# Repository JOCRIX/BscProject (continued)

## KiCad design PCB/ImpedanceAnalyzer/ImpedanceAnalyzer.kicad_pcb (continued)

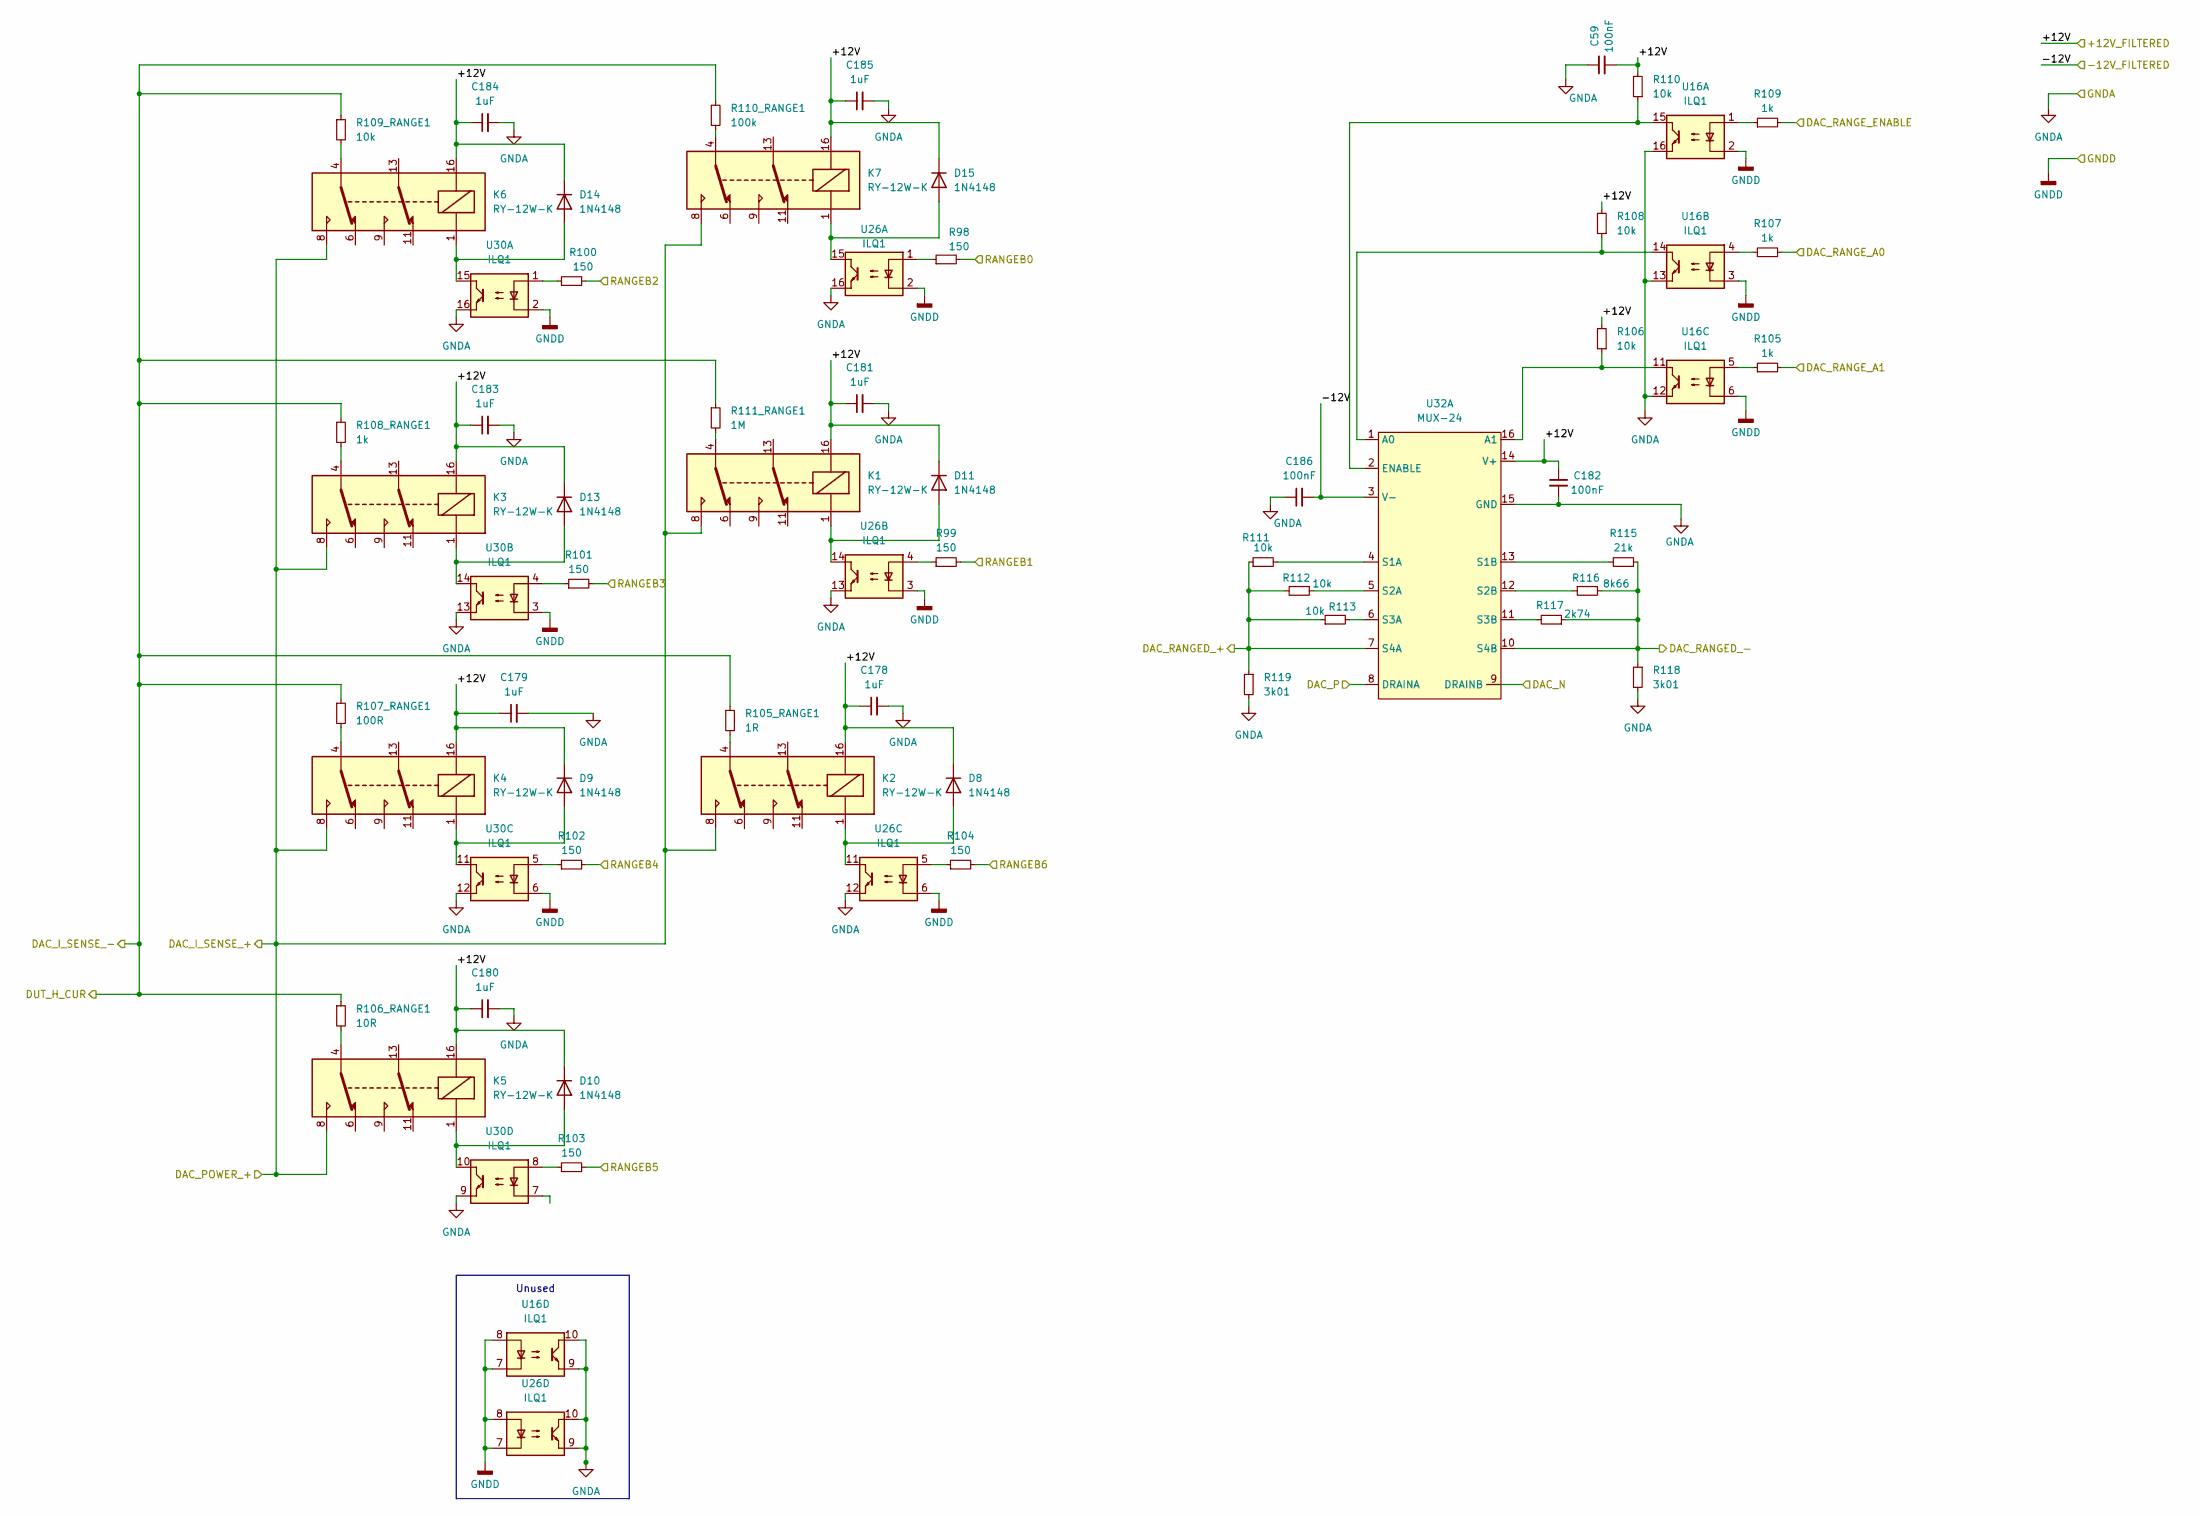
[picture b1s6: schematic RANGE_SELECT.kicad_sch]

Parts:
C59, C182, C186: 100nF; C_0805_2012Metric_Pad1.18x1.45mm_HandSolder
C178, C179, C180, C181, C183, C184, C185: 1uF; C_0805_2012Metric_Pad1.18x1.45mm_HandSolder
D8, D9, D10, D11, D13, D14, D15: 1N4148; D_DO-35_SOD27_P7.62mm_Horizontal
K1, K2, K3, K4, K5, K6, K7: RY-12W-K; RELAY_RY-12W-K
R98, R99, R100, R101, R102, R103, R104: 150; R_0805_2012Metric_Pad1.20x1.40mm_HandSolder
R105, R107, R109: 1k; R_0805_2012Metric_Pad1.20x1.40mm_HandSolder
R105_RANGE1: 1R; R_Axial_DIN0516_L15.5mm_D5.0mm_P20.32mm_Horizontal
R106, R108, R110: 10k; R_0805_2012Metric_Pad1.20x1.40mm_HandSolder
R106_RANGE1: 10R; R_Axial_DIN0207_L6.3mm_D2.5mm_P10.16mm_Horizontal
R107_RANGE1: 100R; R_Axial_DIN0207_L6.3mm_D2.5mm_P10.16mm_Horizontal
R108_RANGE1: 1k; R_Axial_DIN0207_L6.3mm_D2.5mm_P10.16mm_Horizontal
R109_RANGE1, R111, R112, R113: 10k; R_Axial_DIN0207_L6.3mm_D2.5mm_P10.16mm_Horizontal
R110_RANGE1: 100k; R_Axial_DIN0207_L6.3mm_D2.5mm_P10.16mm_Horizontal
R111_RANGE1: 1M; R_Axial_DIN0207_L6.3mm_D2.5mm_P10.16mm_Horizontal
R115: 21k; R_Axial_DIN0207_L6.3mm_D2.5mm_P10.16mm_Horizontal
R116: 8k66; R_Axial_DIN0207_L6.3mm_D2.5mm_P10.16mm_Horizontal
R117: 2k74; R_Axial_DIN0207_L6.3mm_D2.5mm_P10.16mm_Horizontal
R118, R119: 3k01; R_Axial_DIN0207_L6.3mm_D2.5mm_P10.16mm_Horizontal
U16, U26, U30: ILQ1; DIP-16_W7.62mm
U32: MUX-24; DIP-16_W7.62mm

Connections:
/ADC Range/+12V: C59.2, C178.1, C179.1, C180.1, C181.1, C182.1, C183.1, C184.1, C185.1, D8.1 (K), D9.1 (K), D10.1 (K), D11.1 (K), D13.1 (K), D14.1 (K), D15.1 (K), K1.16, K2.16, K3.16, K4.16, K5.16, K6.16, K7.16, R106.2, R108.2, R110.2, U32.14 (V+); also elsewhere on the board
/ADC Range/-12V: C186.2, U32.3 (V-); also elsewhere on the board
/ADC Range/DUT_I_SENSE_+: K1.8, K2.8, K3.8, K4.8, K5.8, K6.8, K7.8; also elsewhere on the board
/ADC Range/DUT_I_SENSE_-: R105_RANGE1.1, R106_RANGE1.1, R107_RANGE1.1, R108_RANGE1.1, R109_RANGE1.1, R110_RANGE1.1, R111_RANGE1.1; also elsewhere on the board
/DAC Power Amp/DAC_RANGED_+: R111.1, R112.2, R113.1, R119.1, U32.7 (S4A); also elsewhere on the board
/DAC Power Amp/DAC_RANGED_-: R115.1, R116.2, R117.1, R118.1, U32.10 (S4B); also elsewhere on the board
/DAC/DAC_N: U32.9 (DRAINB); also elsewhere on the board
/DAC/DAC_P: U32.8 (DRAINA); also elsewhere on the board
/DRA0: R107.2; also elsewhere on the board
/DRA1: R105.2; also elsewhere on the board
/DRE: R109.2; also elsewhere on the board
/RB0: R98.2; also elsewhere on the board
/RB1: R99.2; also elsewhere on the board
/RB2: R100.2; also elsewhere on the board
/RB3: R101.2; also elsewhere on the board
/RB4: R102.2; also elsewhere on the board
/RB5: R103.2; also elsewhere on the board
/RB6: R104.2; also elsewhere on the board
unnamed: D8.2 (A), K2.1, U26.11
unnamed: D9.2 (A), K4.1, U30.11
unnamed: D10.2 (A), K5.1, U30.10
unnamed: D11.2 (A), K1.1, U26.14
unnamed: D13.2 (A), K3.1, U30.14
unnamed: D14.2 (A), K6.1, U30.15
unnamed: D15.2 (A), K7.1, U26.15
unnamed: K1.4, R111_RANGE1.2
unnamed: K2.4, R105_RANGE1.2
unnamed: K3.4, R108_RANGE1.2
unnamed: K4.4, R107_RANGE1.2
unnamed: K5.4, R106_RANGE1.2
unnamed: K6.4, R109_RANGE1.2
unnamed: K7.4, R110_RANGE1.2
unnamed: R98.1, U26.1
unnamed: R99.1, U26.4
unnamed: R100.1, U30.1
unnamed: R101.1, U30.4
unnamed: R102.1, U30.5
unnamed: R103.1, U30.8
unnamed: R104.1, U26.5
unnamed: R105.1, U16.5
unnamed: R107.1, U16.4
unnamed: R109.1, U16.1
unnamed: R108.1, U16.14, U32.1 (A0)
unnamed: R106.1, U16.11, U32.16 (A1)
unnamed: R110.1, U16.15, U32.2 (ENABLE)
unnamed: R111.2, U32.4 (S1A)
unnamed: R115.2, U32.13 (S1B)
unnamed: R112.1, U32.5 (S2A)
unnamed: R116.1, U32.12 (S2B)
unnamed: R113.2, U32.6 (S3A)
unnamed: R117.2, U32.11 (S3B)

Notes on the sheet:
Unused

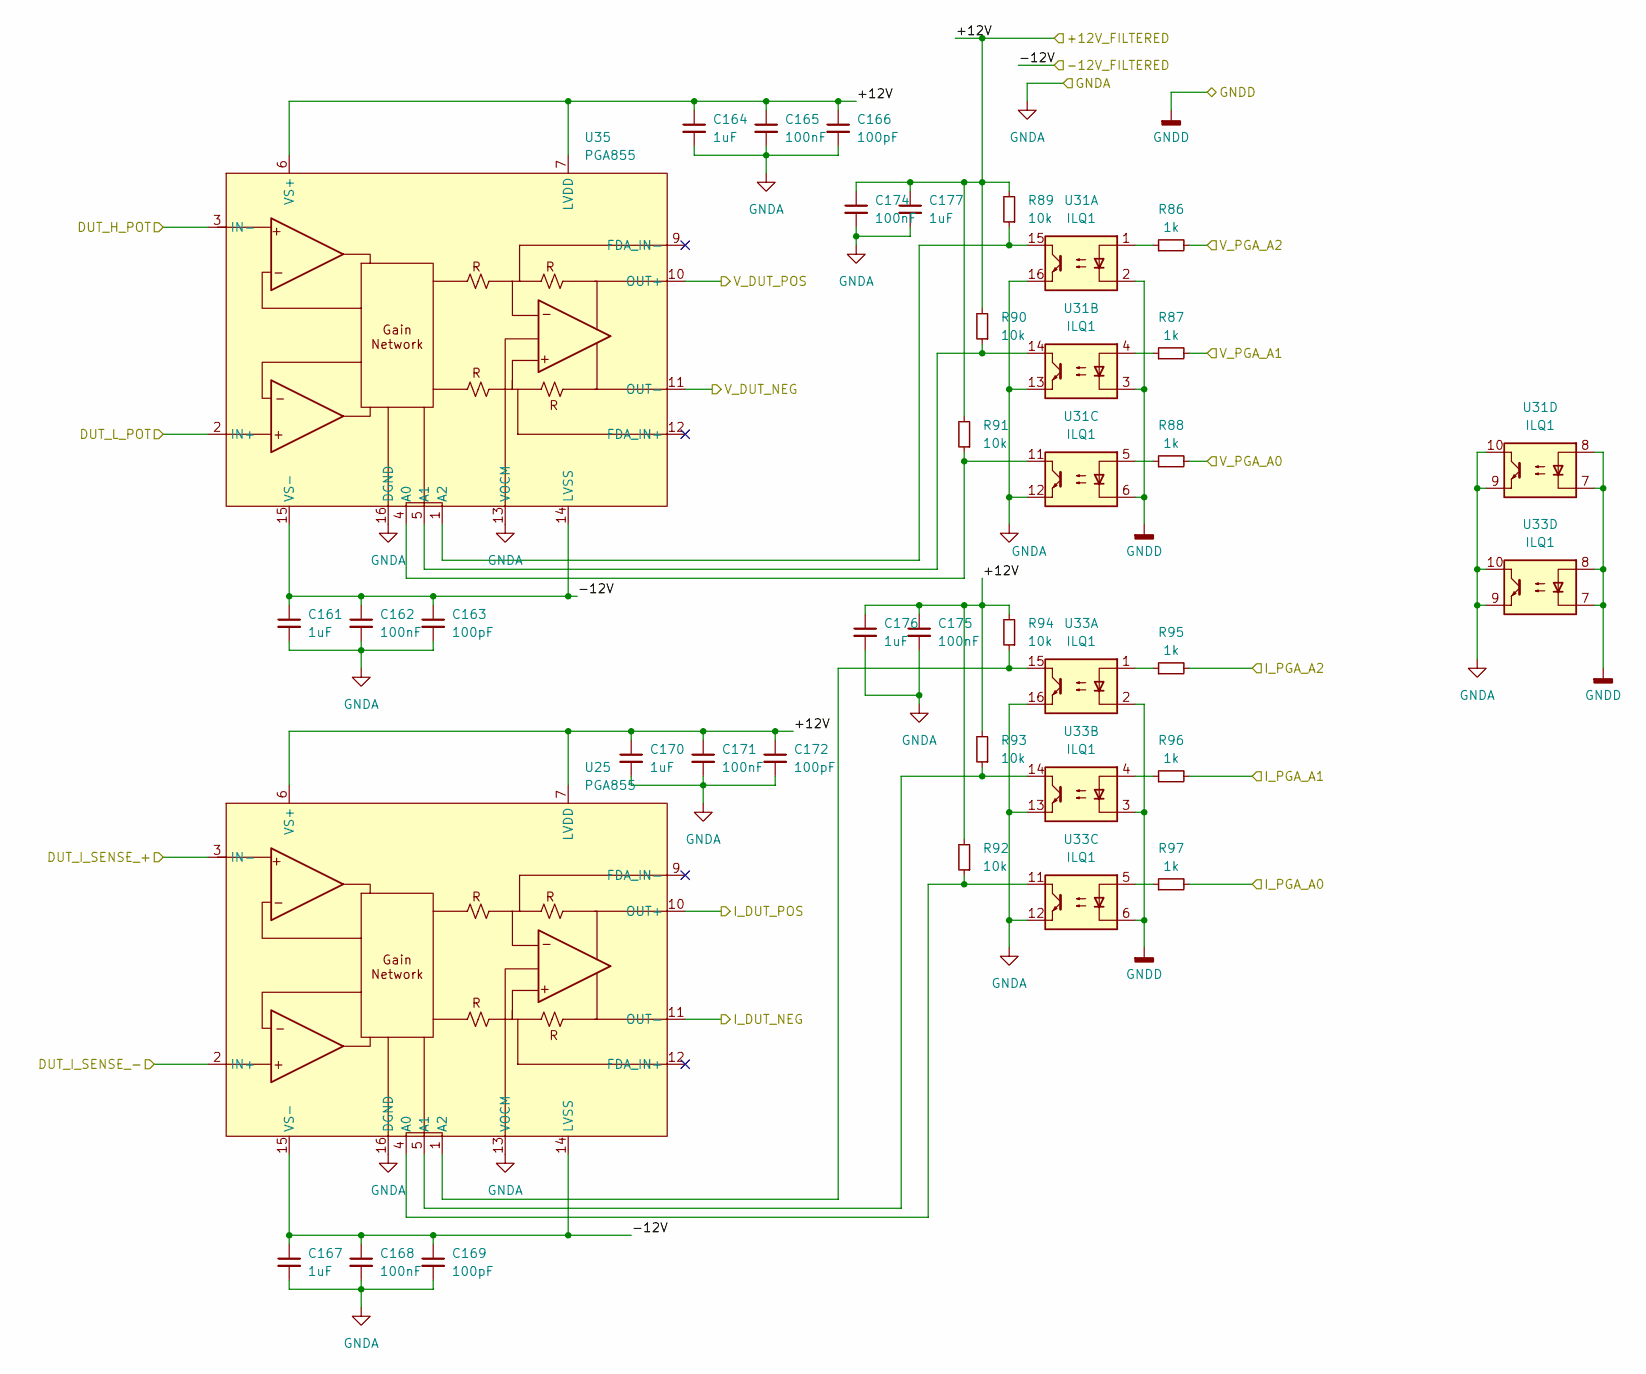
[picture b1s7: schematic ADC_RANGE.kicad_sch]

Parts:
C161, C164, C167, C170, C176, C177: 1uF; C_0805_2012Metric_Pad1.18x1.45mm_HandSolder
C162, C165, C168, C171, C174, C175: 100nF; C_0805_2012Metric_Pad1.18x1.45mm_HandSolder
C163, C166, C169, C172: 100pF; C_Disc_D3.4mm_W2.1mm_P2.50mm
R86, R87, R88, R95, R96, R97: 1k; R_0805_2012Metric_Pad1.20x1.40mm_HandSolder
R89, R90, R91, R92, R93, R94: 10k; R_0805_2012Metric_Pad1.20x1.40mm_HandSolder
U25, U35: PGA855; VQFN-16-1EP_3x3mm_P0.5mm_EP1.45x1.45mm
U31, U33: ILQ1; DIP-16_W7.62mm

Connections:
/ADC Range/+12V: C164.1, C165.1, C166.1, C170.1, C171.1, C172.1, C174.1, C175.1, C176.1, C177.1, R89.2, R90.2, R91.2, R92.2, R93.2, R94.2, U25.6 (VS+), U25.7 (LVDD), U35.6 (VS+), U35.7 (LVDD); also elsewhere on the board
/ADC Range/-12V: C161.1, C162.1, C163.1, C167.1, C168.1, C169.1, U25.14 (LVSS), U25.15 (VS-), U35.14 (LVSS), U35.15 (VS-); also elsewhere on the board
/ADC Range/DUT_H_POT: U35.3 (IN-); also elsewhere on the board
/ADC Range/DUT_I_SENSE_+: U25.3 (IN-); also elsewhere on the board
/ADC Range/DUT_I_SENSE_-: U25.2 (IN+); also elsewhere on the board
/ADC Range/DUT_L_POT: U35.2 (IN+); also elsewhere on the board
/ADC Range/I_DUT_NEG: U25.11 (OUT-); also elsewhere on the board
/ADC Range/I_DUT_POS: U25.10 (OUT+); also elsewhere on the board
/ADC Range/I_PGA_A0: R97.2; also elsewhere on the board
/ADC Range/I_PGA_A1: R96.2; also elsewhere on the board
/ADC Range/I_PGA_A2: R95.2; also elsewhere on the board
/ADC Range/V_DUT_NEG: U35.11 (OUT-); also elsewhere on the board
/ADC Range/V_DUT_POS: U35.10 (OUT+); also elsewhere on the board
/ADC Range/V_PGA_A0: R88.2; also elsewhere on the board
/ADC Range/V_PGA_A1: R87.2; also elsewhere on the board
/ADC Range/V_PGA_A2: R86.2; also elsewhere on the board
unnamed: R86.1, U31.1
unnamed: R87.1, U31.4
unnamed: R88.1, U31.5
unnamed: R95.1, U33.1
unnamed: R96.1, U33.4
unnamed: R97.1, U33.5
unnamed: R92.1, U25.4 (A0), U33.11
unnamed: R93.1, U25.5 (A1), U33.14
unnamed: R94.1, U25.1 (A2), U33.15
unnamed: R91.1, U31.11, U35.4 (A0)
unnamed: R90.1, U31.14, U35.5 (A1)
unnamed: R89.1, U31.15, U35.1 (A2)

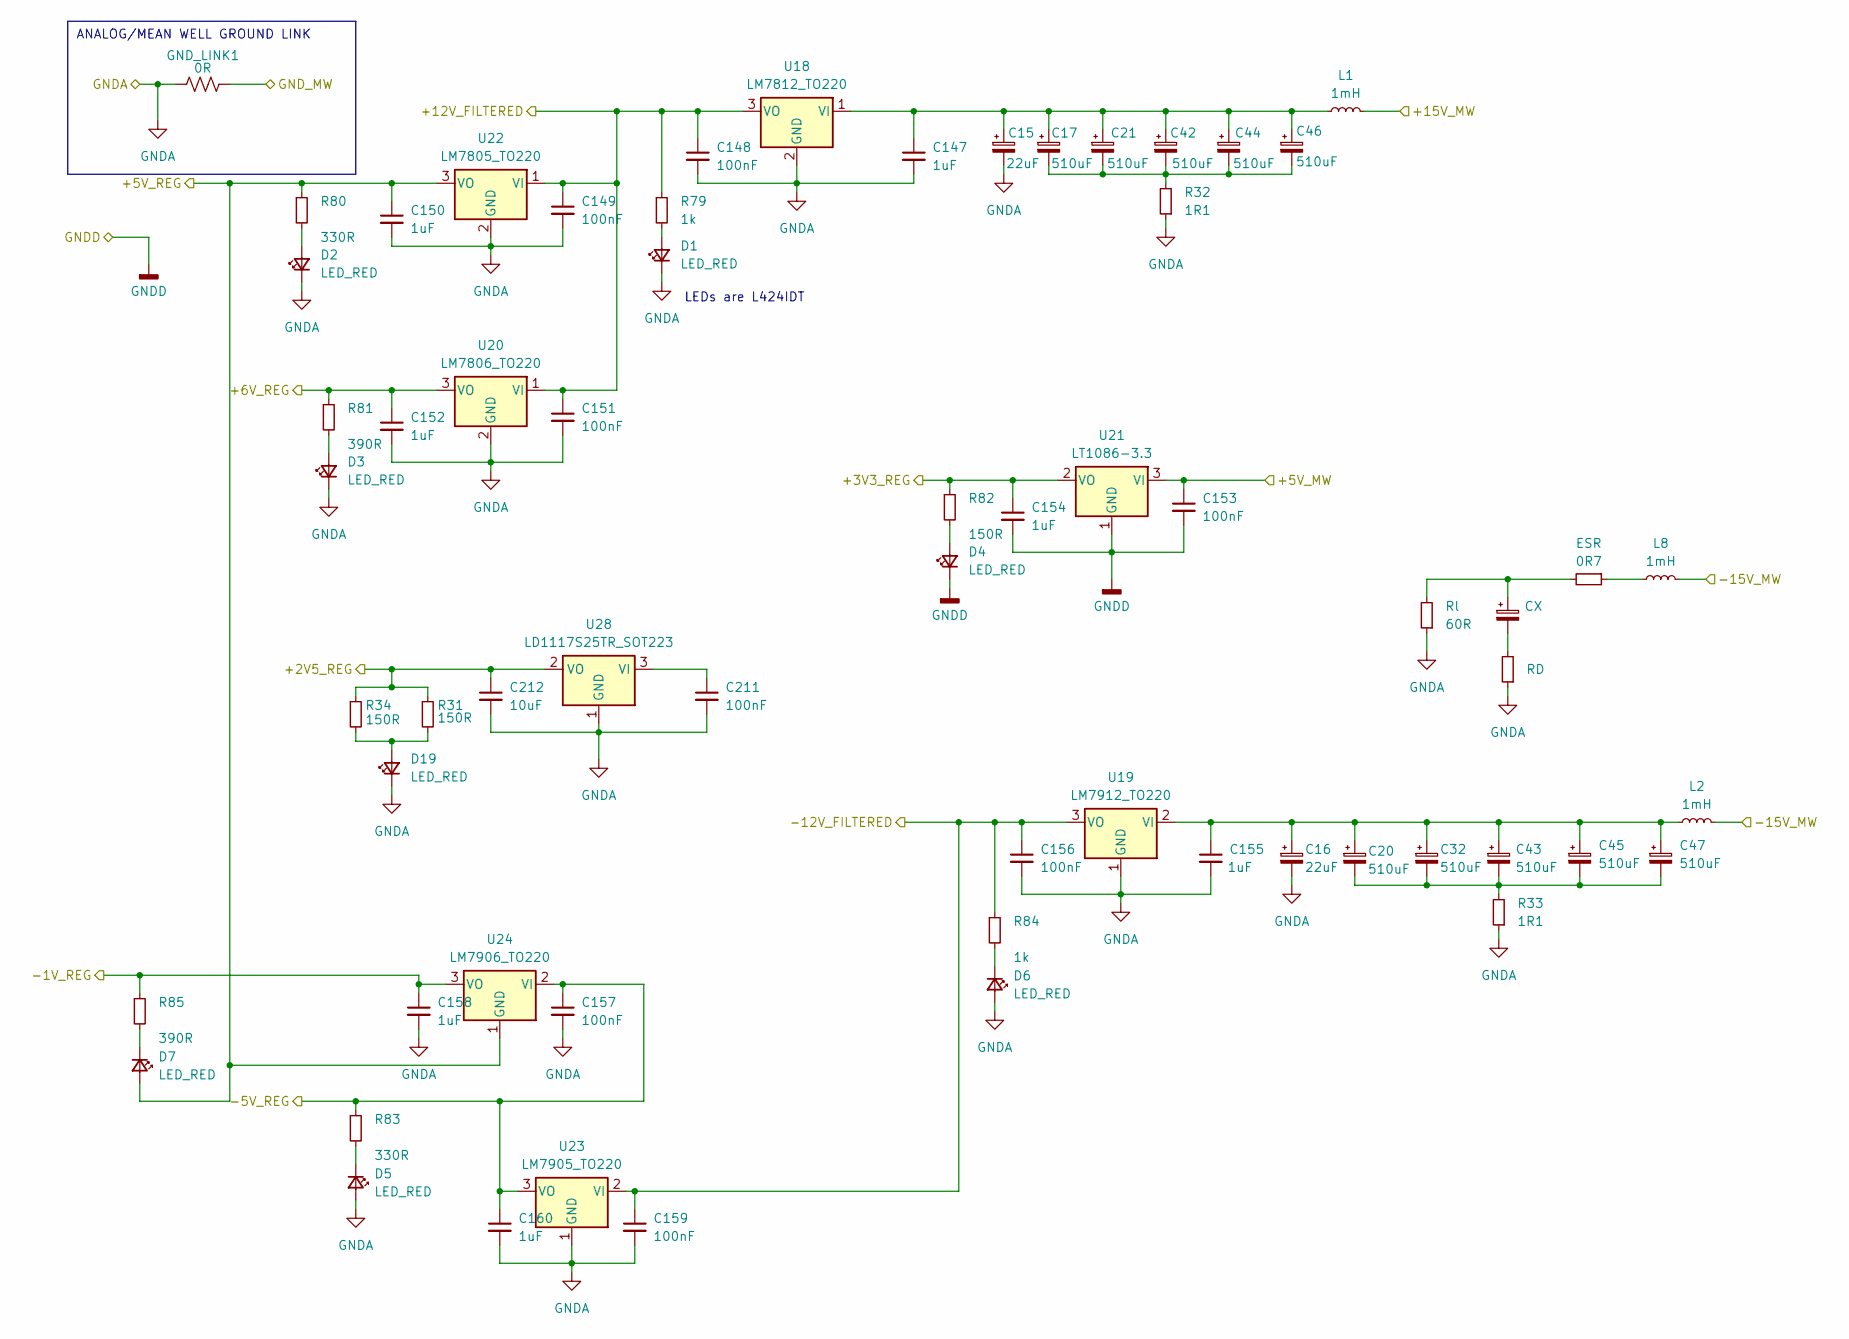
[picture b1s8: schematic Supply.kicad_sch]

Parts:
C15, C16: 22uF; CP_Radial_D6.3mm_P2.50mm
C17, C20, C21, C32, C42, C43, C44, C45, C46, C47: 510uF; CP_Radial_D10.0mm_P5.00mm
C147, C150, C152, C154, C155, C158, C160: 1uF; C_0805_2012Metric_Pad1.18x1.45mm_HandSolder
C148, C149, C151, C153, C156, C157, C159, C211: 100nF; C_0805_2012Metric_Pad1.18x1.45mm_HandSolder
C212: 10uF; C_1210_3225Metric
CX: CX; CP_Radial_D10.0mm_P5.00mm
D1, D2, D3, D4, D5, D6, D7, D19: LED_RED; LED_D2.0mm_W4.0mm_H2.8mm_FlatTop
ESR: 0R7; R_Axial_DIN0207_L6.3mm_D2.5mm_P10.16mm_Horizontal
GND_LINK1: 0R; Resistor SMD - 2818
L1, L2, L8: 1mH; INDRD1000W100D1800H2550 - AIUR-15-102K
R31, R34, R82: 150R; R_Axial_DIN0207_L6.3mm_D2.5mm_P10.16mm_Horizontal
R32, R33: 1R1; R_Axial_DIN0207_L6.3mm_D2.5mm_P10.16mm_Horizontal
R35: RD; R_Axial_DIN0207_L6.3mm_D2.5mm_P10.16mm_Horizontal
R79, R84: 1k; R_Axial_DIN0207_L6.3mm_D2.5mm_P10.16mm_Horizontal
R80, R83: 330R; R_Axial_DIN0207_L6.3mm_D2.5mm_P10.16mm_Horizontal
R81, R85: 390R; R_Axial_DIN0207_L6.3mm_D2.5mm_P10.16mm_Horizontal
Rl: 60R; R_Axial_DIN0207_L6.3mm_D2.5mm_P10.16mm_Horizontal
U18: LM7812_TO220; TO-220-3_Vertical
U19: LM7912_TO220; TO-220-3_Vertical
U20: LM7806_TO220; TO-220-3_Vertical
U21: LT1086-3.3; TO-220-3_Vertical
U22: LM7805_TO220; TO-220-3_Vertical
U23: LM7905_TO220; TO-220-3_Vertical
U24: LM7906_TO220; TO-220-3_Vertical
U28: LD1117S25TR_SOT223; SOT-223-3_TabPin2

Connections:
/+5V_MW: C153.1, U21.3 (VI); also elsewhere on the board
/+15V_MW: L1.2; also elsewhere on the board
/-15V_MW: L2.2, L8.2; also elsewhere on the board
/ADC Range/+12V: C148.1, C149.1, C151.1, R79.1, U18.3 (VO), U20.1 (VI), U22.1 (VI); also elsewhere on the board
/ADC Range/-12V: C156.1, C159.1, R84.1, U19.3 (VO), U23.2 (VI); also elsewhere on the board
/ADC/+2V5: C212.1, R31.1, R34.1, U28.2 (VO); also elsewhere on the board
/ADC/+6V: C152.1, R81.1, U20.3 (VO); also elsewhere on the board
/ADC/-1V: C158.1, R85.1, U24.3 (VO); also elsewhere on the board
/Digital/+3V3: C154.1, R82.1, U21.2 (VO); also elsewhere on the board
/GND_MW: GND_LINK1.2; also elsewhere on the board
unnamed: C17.2, C21.2, C42.2, C44.2, C46.2, R32.2
unnamed: CX.1, ESR.2, Rl.2
unnamed: CX.2, R35.2
unnamed: D1.2 (A), R79.2
unnamed: D2.2 (A), R80.2
unnamed: D3.2 (A), R81.2
unnamed: D4.2 (A), R82.2
unnamed: D5.1 (K), R83.2
unnamed: D6.1 (K), R84.2
unnamed: D7.1 (K), R85.2
unnamed: D19.2 (A), R31.2, R34.2
unnamed: ESR.1, L8.1
unnamed: C15.1, C17.1, C21.1, C42.1, C44.1, C46.1, C147.1, L1.1, U18.1 (VI)

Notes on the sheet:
LEDs are L424IDT
ANALOG/MEAN WELL GROUND LINK

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
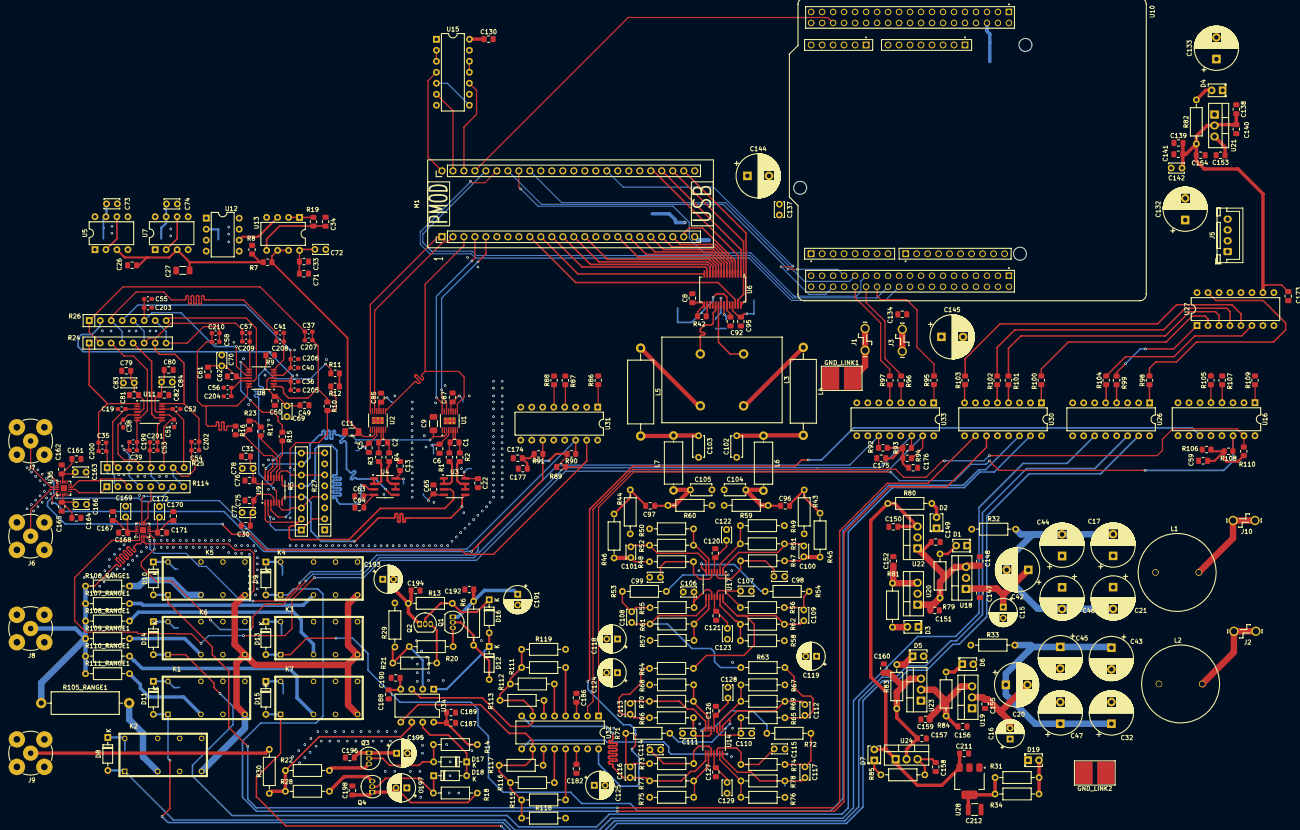
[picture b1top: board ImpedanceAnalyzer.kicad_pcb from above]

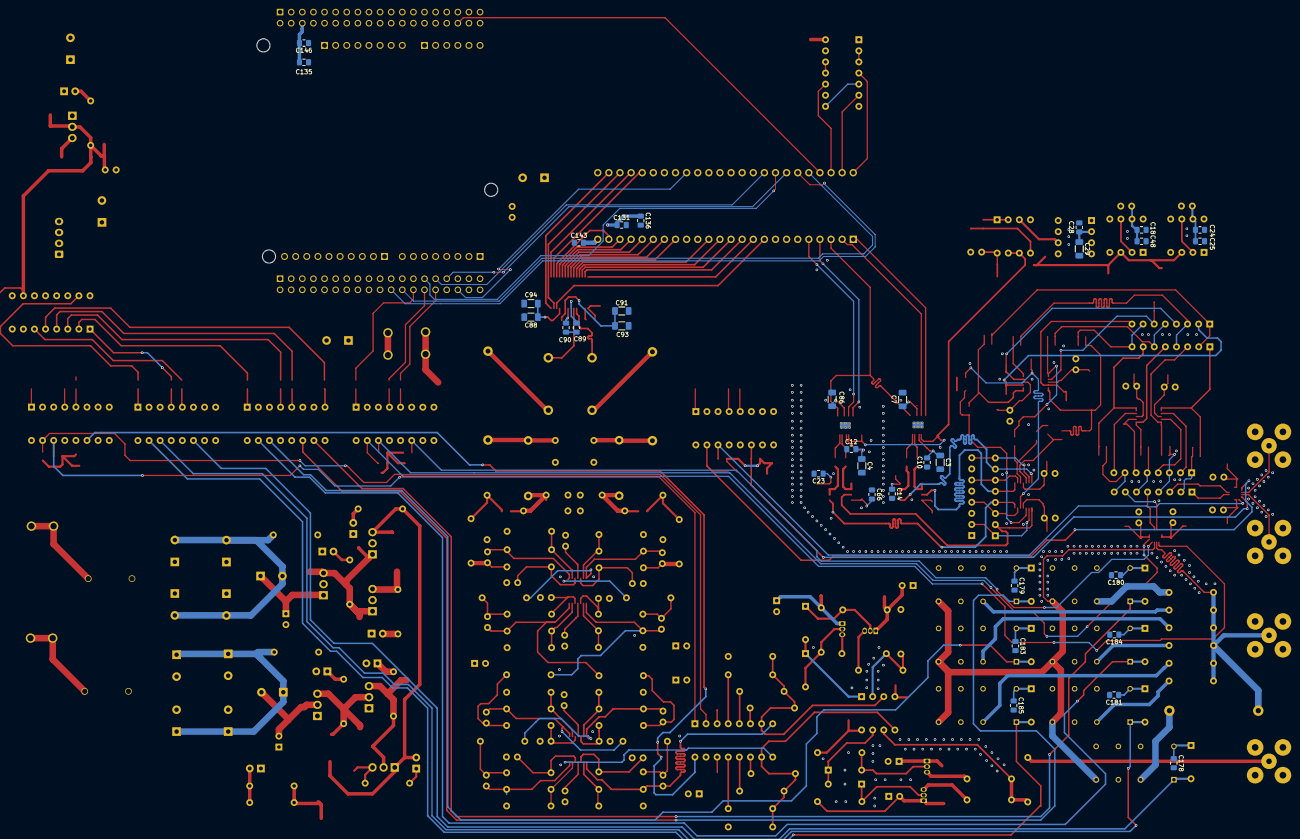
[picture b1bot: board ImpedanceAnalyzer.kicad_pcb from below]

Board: 4 copper layers, 411 parts (33 on the bottom side), 258 nets.

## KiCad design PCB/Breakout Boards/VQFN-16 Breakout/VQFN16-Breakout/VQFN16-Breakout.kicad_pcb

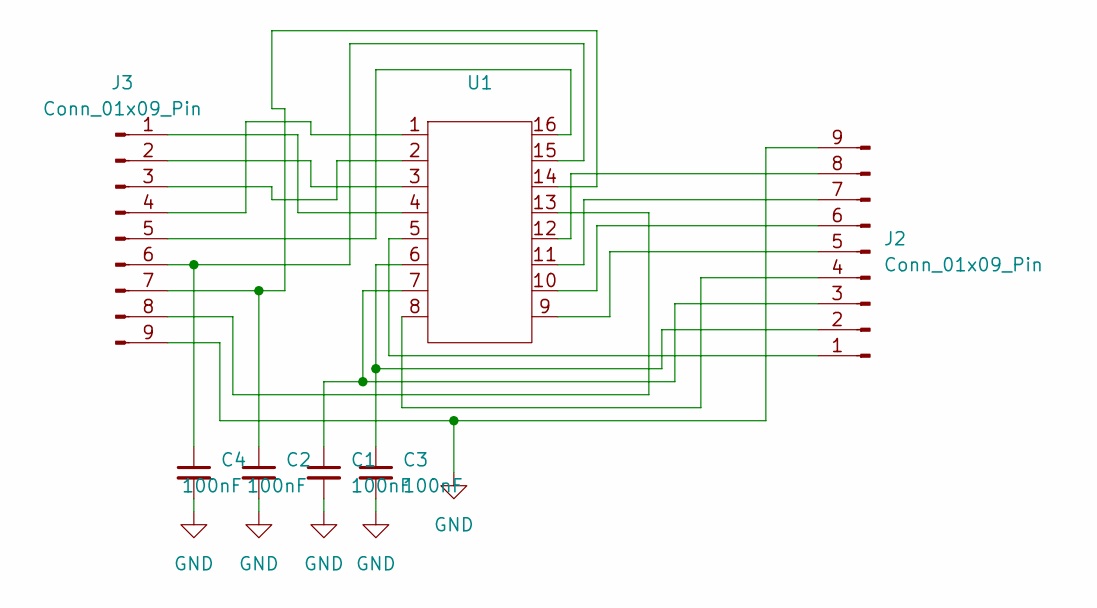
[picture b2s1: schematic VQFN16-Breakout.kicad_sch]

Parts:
C1, C2, C3, C4: 100nF; C_0805_2012Metric
J2, J3: Conn_01x09_Pin; PinHeader_1x09_P2.54mm_Vertical
U1: VQFN-16-1EP_3x3mm_P0.5mm_EP1.45x1.45mm

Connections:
GND: C1.2, C2.2, C3.2, C4.2, J2.9, J3.9
unnamed: J2.1, U1.5
unnamed: C3.1, J2.2, U1.6
unnamed: C1.1, J2.3, U1.7
unnamed: J2.4, U1.8
unnamed: J2.5, U1.9
unnamed: J2.6, U1.10
unnamed: J2.7, U1.11
unnamed: J2.8, U1.12
unnamed: J3.1, U1.4
unnamed: J3.2, U1.3
unnamed: J3.3, U1.2
unnamed: J3.4, U1.1
unnamed: J3.5, U1.16
unnamed: C4.1, J3.6, U1.15
unnamed: C2.1, J3.7, U1.14
unnamed: J3.8, U1.13

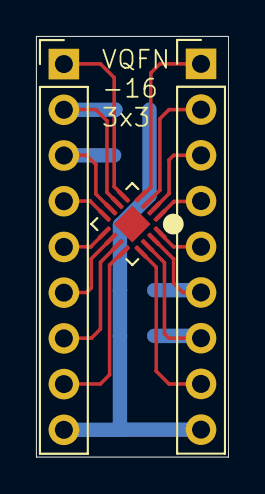
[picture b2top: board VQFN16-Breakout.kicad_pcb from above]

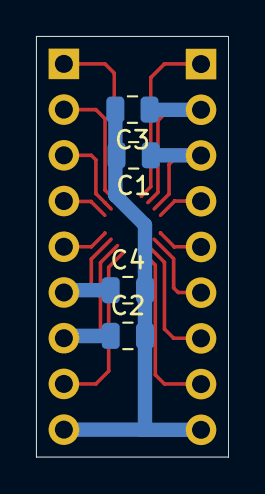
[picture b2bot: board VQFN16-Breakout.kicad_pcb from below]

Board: 2 copper layers, 10.7 x 23.4 mm, 7 parts (4 on the bottom side), 17 nets.

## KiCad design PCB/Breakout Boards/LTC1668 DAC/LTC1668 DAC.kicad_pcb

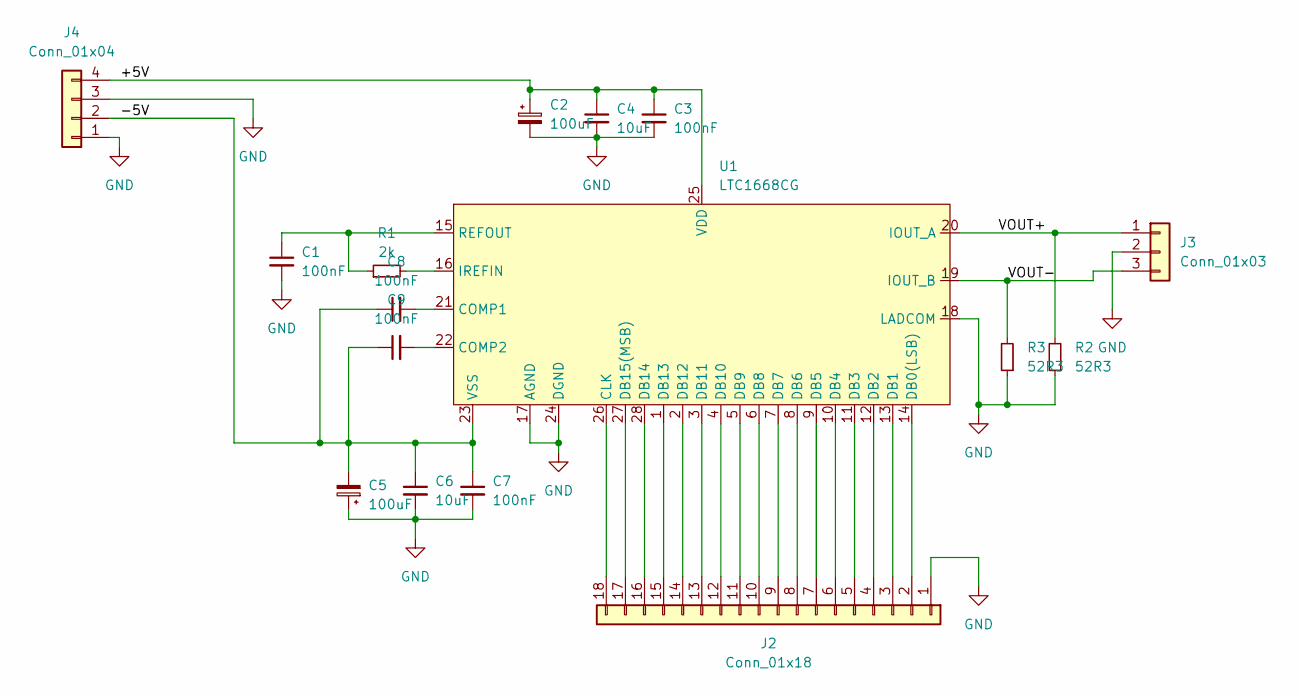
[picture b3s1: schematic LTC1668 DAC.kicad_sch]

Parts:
C1, C3, C7, C8, C9: 100nF; C_0805_2012Metric_Pad1.18x1.45mm_HandSolder
C2, C5: 100uF; CP_Radial_D6.3mm_P2.50mm
C4, C6: 10uF; C_1206_3216Metric_Pad1.33x1.80mm_HandSolder
J2: Conn_01x18; PinHeader_1x18_P2.54mm_Vertical
J3: Conn_01x03; PinHeader_1x03_P2.54mm_Vertical
J4: Conn_01x04; PinHeader_1x04_P2.54mm_Vertical
R1: 2k; R_0805_2012Metric_Pad1.20x1.40mm_HandSolder
R2, R3: 52R3; R_0805_2012Metric_Pad1.20x1.40mm_HandSolder
U1: LTC1668CG; SSOP-28_5.3x10.2mm_P0.65mm

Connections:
/+5V: C2.1, C3.1, C4.1, J4.4, U1.25 (VDD)
/-5V: C5.2, C6.1, C7.1, C8.1, C9.1, J4.2, U1.23 (VSS)
/VOUT+: J3.1, R2.2, U1.20 (IOUT_A)
/VOUT-: J3.3, R3.2, U1.19 (IOUT_B)
GND: C1.2, C2.2, C3.2, C4.2, C5.1, C6.2, C7.2, J2.1, J3.2, J4.1, J4.3, R2.1, R3.1, U1.17 (AGND), U1.18 (LADCOM), U1.24 (DGND)
unnamed: J2.2, U1.14 (DB0(LSB))
unnamed: J2.3, U1.13 (DB1)
unnamed: J2.4, U1.12 (DB2)
unnamed: J2.5, U1.11 (DB3)
unnamed: J2.6, U1.10 (DB4)
unnamed: J2.7, U1.9 (DB5)
unnamed: J2.8, U1.8 (DB6)
unnamed: J2.9, U1.7 (DB7)
unnamed: J2.10, U1.6 (DB8)
unnamed: J2.11, U1.5 (DB9)
unnamed: J2.12, U1.4 (DB10)
unnamed: J2.13, U1.3 (DB11)
unnamed: J2.14, U1.2 (DB12)
unnamed: J2.15, U1.1 (DB13)
unnamed: J2.16, U1.28 (DB14)
unnamed: J2.17, U1.27 (DB15(MSB))
unnamed: J2.18, U1.26 (CLK)
unnamed: C8.2, U1.21 (COMP1)
unnamed: C9.2, U1.22 (COMP2)
unnamed: R1.2, U1.16 (IREFIN)
unnamed: C1.1, R1.1, U1.15 (REFOUT)

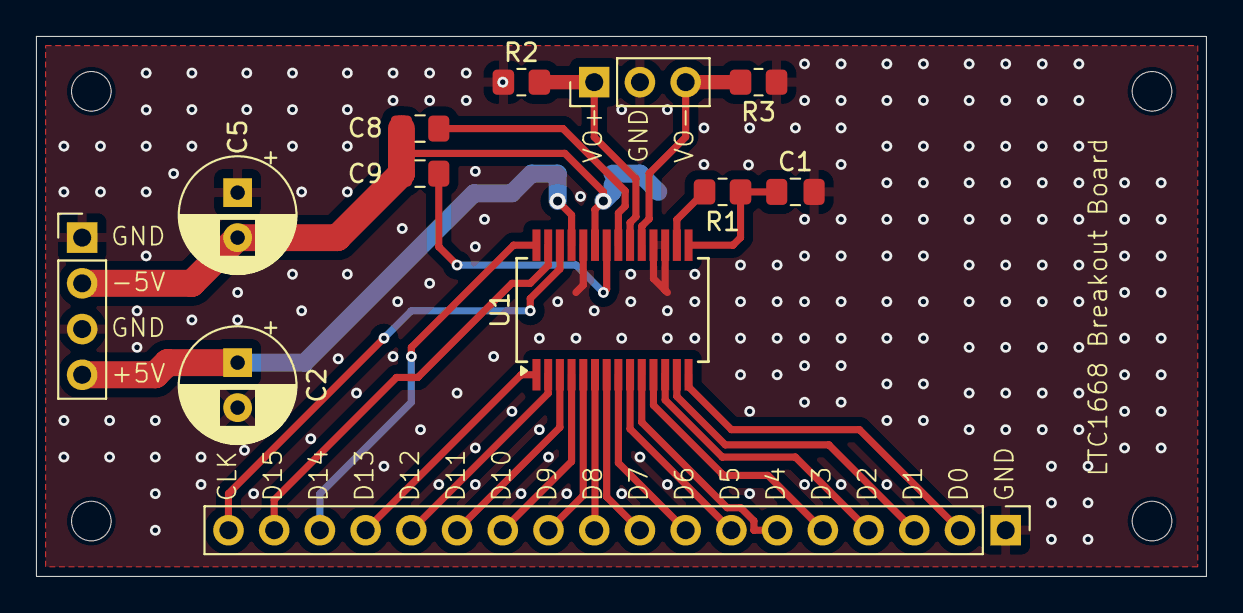
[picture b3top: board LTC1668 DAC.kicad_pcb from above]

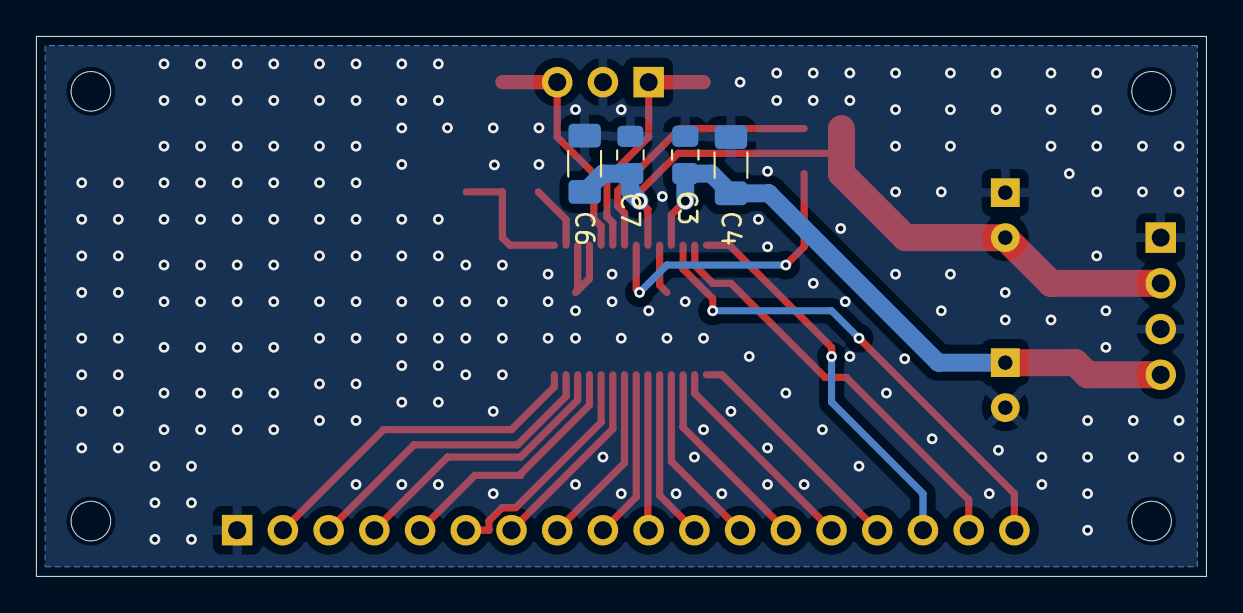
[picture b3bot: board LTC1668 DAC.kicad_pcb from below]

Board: 2 copper layers, 65.0 x 30.0 mm, 16 parts (4 on the bottom side), 26 nets.
